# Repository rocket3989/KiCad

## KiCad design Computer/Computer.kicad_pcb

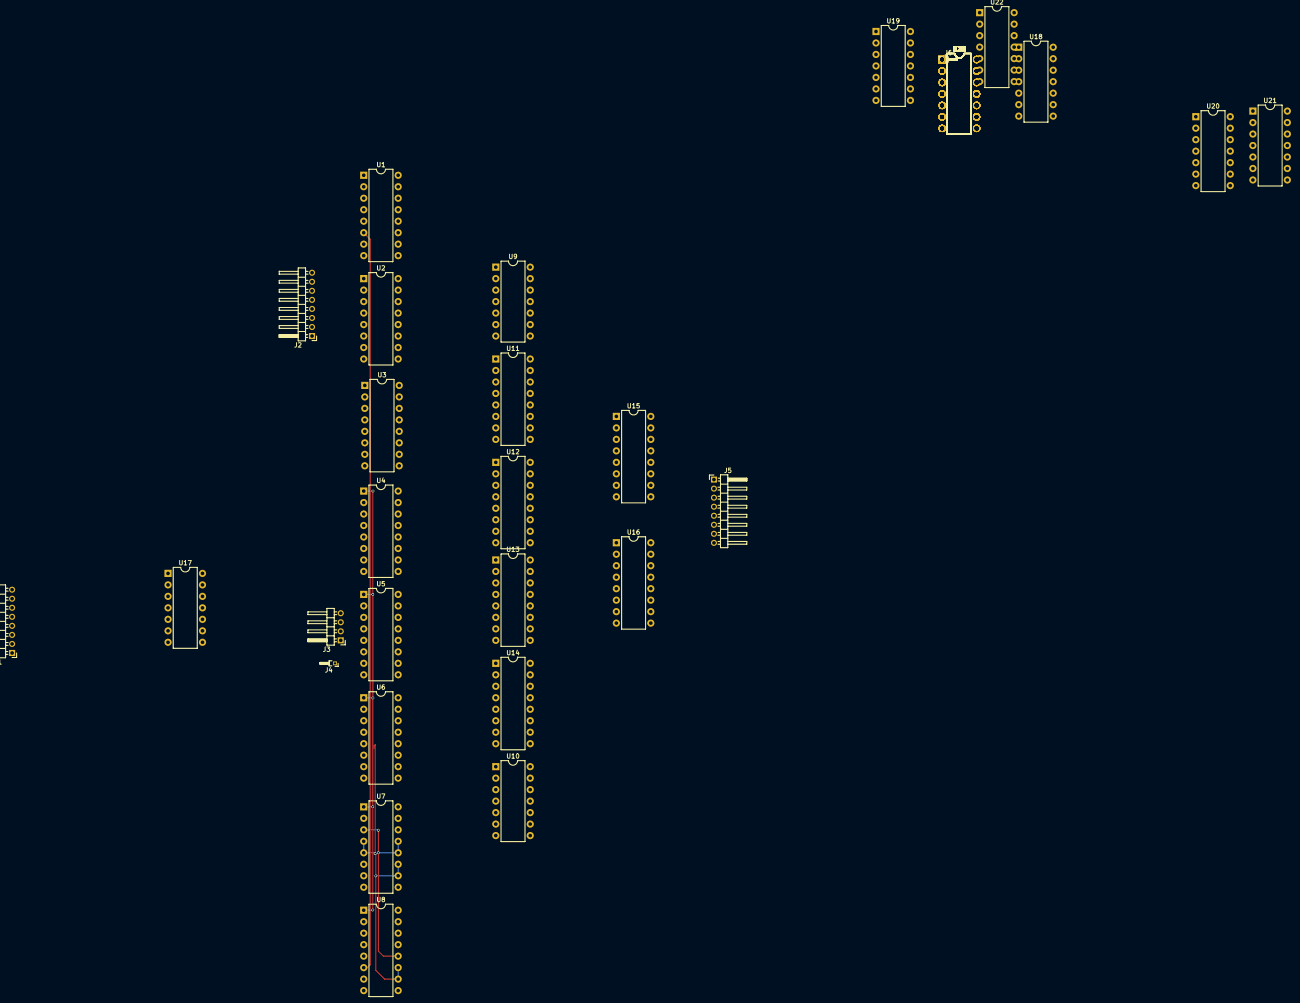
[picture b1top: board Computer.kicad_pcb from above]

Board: 2 copper layers, 44 parts (0 on the bottom side), 57 nets.

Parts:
J1: Conn_01x08; Pin_Header_Angled_1x08_Pitch2.00mm
J2, J5: Conn_01x01; Pin_Header_Angled_1x08_Pitch2.00mm
J3: Conn_01x04; Pin_Header_Angled_1x04_Pitch2.00mm
J4, J6: Conn_01x01; Pin_Header_Angled_1x01_Pitch1.00mm
U1, U2, U3, U4, U5, U6, U7, U8: 74LS253; DIP-16_W7.62mm
U9: 74LS04; DIP-14_W7.62mm
U10: 74LS08; DIP-14_W7.62mm
U11, U12: 74LS283; DIP-16_W7.62mm
U13, U14: 74LS257; DIP-16_W7.62mm
U15: 74LS04; DIP-16_W7.62mm
U16: 74LS244; DIP-16_W7.62mm
U17, U18, U19, U23, U24, U25, U26, U27, U28, U29, U30, U31, U32, U33, U34, U35, U36, U37, U38: 74LS574; DIP-14_W7.62mm
U20: 74LS161; DIP-14_W7.62mm
U21, U22: 74LS154; DIP-14_W7.62mm

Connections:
/ALU/A0: U1.14, U10.4, U11.5, U13.6
/ALU/A1: U2.14, U11.3, U13.2, U13.13
/ALU/A2: U3.14, U11.14, U13.5, U13.10
/ALU/A3: U4.14, U11.12, U13.14, U14.3
/ALU/A4: U5.14, U12.5, U13.11, U14.6
/ALU/A5: U6.14, U12.3, U14.2, U14.13, U17.14
/ALU/A6: U7.14, U12.14, U14.5, U14.10, U17.13
/ALU/A7: U8.14, U10.1, U12.12, U14.14, U17.12
/ALU/AL: J2.1, U17.11
/ALU/ALUB0: U1.9, U11.6
/ALU/ALUB1: U2.9, U11.2
/ALU/ALUB2: U3.9, U11.15
/ALU/ALUB3: U4.9, U11.11
/ALU/ALUB4: U5.9, U12.6
/ALU/ALUB5: U6.9, U12.2
/ALU/ALUB6: U7.9, U12.15
/ALU/ALUB7: U8.9, U12.11
/ALU/BUS0: J1.8, U1.2, U17.2
/ALU/BUS1: J1.7, U2.2, U17.3
/ALU/BUS2: J1.6, U3.2, U17.4
/ALU/BUS3: J1.5, U4.2, U17.5
/ALU/BUS4: J1.4, U5.2, U17.6
/ALU/BUS5: J1.3, U6.2, U17.7, U18.14
/ALU/BUS6: J1.2, U7.2, U17.8, U18.13
/ALU/BUS7: J1.1, U8.2, U17.9, U18.12
/ALU/OB: J6.1, U18.1
/ALU/OL: J5.1, U18.11
/ALU/OUT0: U1.7, U13.4, U18.2
/ALU/OUT1: U2.7, U13.7, U16.16, U18.3
/ALU/OUT2: U3.7, U13.12, U16.14, U18.4
/ALU/OUT3: U4.7, U13.9, U16.12, U18.5
/ALU/OUT4: U5.7, U14.4, U16.9, U18.6
/ALU/OUT5: U6.7, U14.7, U16.7, U18.7
/ALU/OUT6: U7.7, U14.12, U16.5, U18.8
/ALU/OUT7: U8.7, U14.9, U16.3, U18.9
/ALU/S0: J3.4, U1.3, U1.12, U1.13, U2.3, U2.12, U2.13, U3.3, U3.12, U3.13, U4.3, U4.12, U4.13, U5.3, U5.12, U5.13, U6.3, U6.12, U6.13, U7.3, U7.12, U7.13, U8.3, U8.12, U8.13, U9.1, U13.1, U14.1
/ALU/S1: J3.3, U1.4, U1.5, U1.10, U1.11, U2.4, U2.5, U2.10, U2.11, U3.4, U3.5, U3.10, U3.11, U4.4, U4.5, U4.10, U4.11, U5.4, U5.5, U5.10, U5.11, U6.4, U6.5, U6.10, U6.11, U7.4, U7.5, U7.10, U7.11, U8.4, U8.5, U8.10, U8.11, U10.2, U10.5
/ALU/S2: J3.2, U1.6, U2.6, U3.6, U4.6, U5.6, U6.6, U7.6, U8.6, U10.10, U15.5
/ALU/S3: J3.1, U1.1, U2.1, U3.1, U4.1, U5.1, U6.1, U7.1, U8.1, U10.9, U10.12
GND: J4.1, U1.8, U1.15, U2.8, U2.15, U3.8, U3.15, U4.8, U4.15, U5.8, U5.15, U6.8, U6.15, U7.8, U7.15, U8.8, U8.15, U9.7, U10.7, U11.8, U12.8, U13.8, U14.8, U15.7, U16.10, U17.1, U17.10, U18.10, U19.10, U20.8, U21.12, U22.12, U23.10, U24.10, U25.10, U26.10, U27.10, U28.10, U29.10, U30.10, U31.10, U32.10, U33.10, U34.10, U35.10, U36.10, U37.10, U38.10
unnamed: U10.3, U13.3
unnamed: U10.6, U14.11
unnamed: U10.8, U15.1
unnamed: U10.11, U15.3
unnamed: U10.13, U15.6
unnamed: U11.1, U16.4
unnamed: U11.4, U16.2
unnamed: U9.2, U11.7
unnamed: U11.9, U12.7
unnamed: U11.10, U16.8
unnamed: U11.13, U16.6
unnamed: U12.1, U16.13
unnamed: U12.4, U16.11
unnamed: U12.13, U16.15
unnamed: U13.15, U14.15, U15.2
unnamed: U15.4, U16.1
VCC: U1.16, U2.16, U3.16, U4.16, U5.16, U6.16, U7.16, U8.16, U9.14, U10.14, U11.16, U12.16, U13.16, U14.16, U15.14

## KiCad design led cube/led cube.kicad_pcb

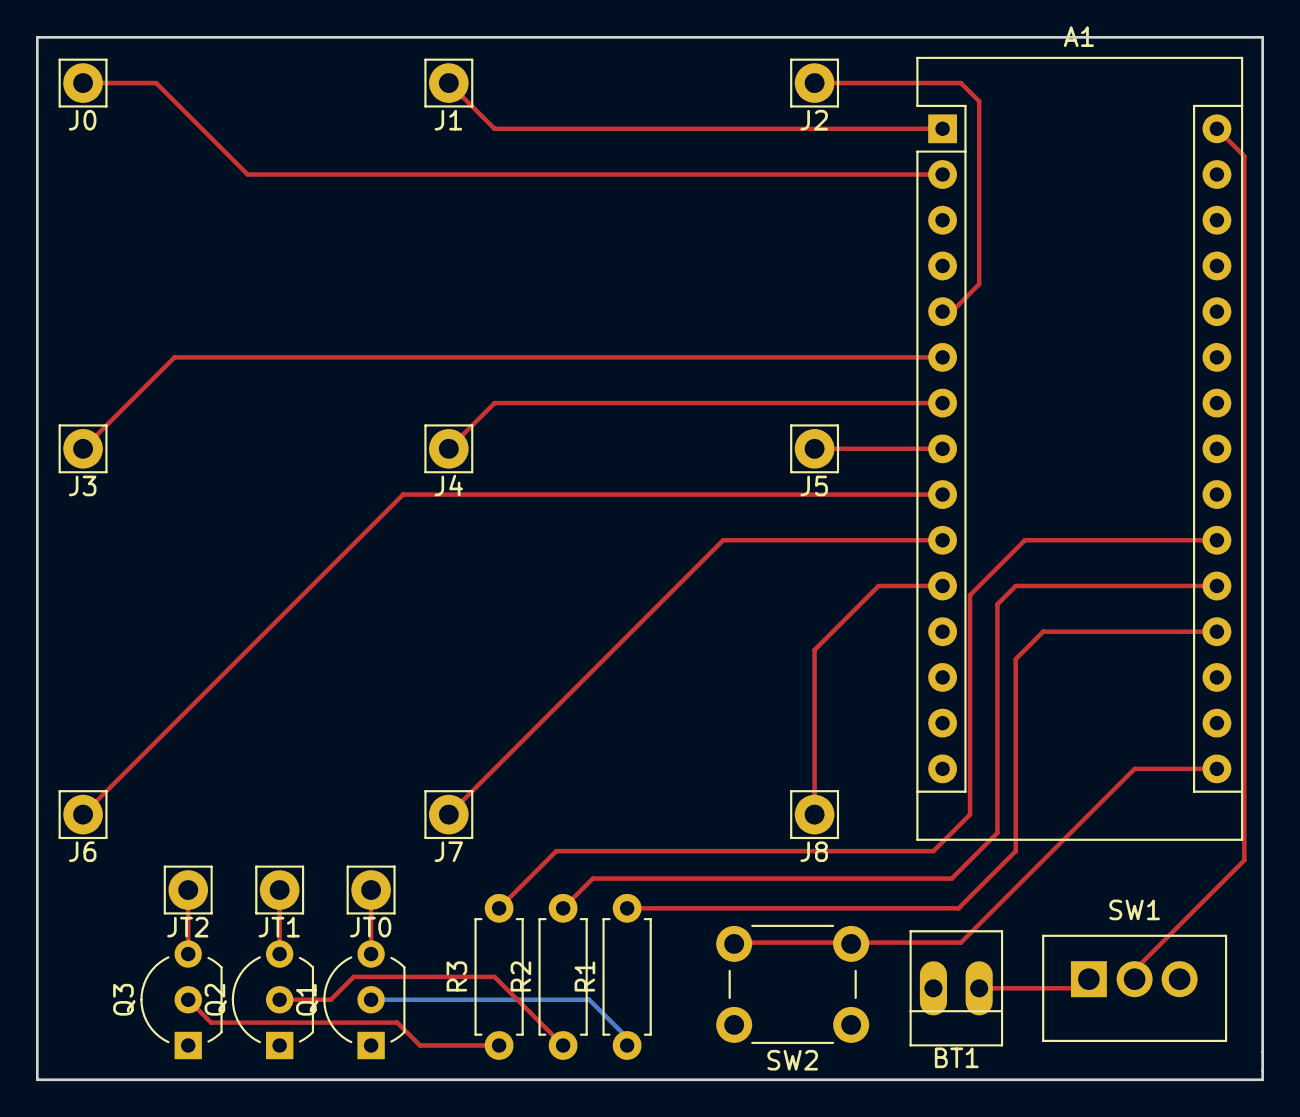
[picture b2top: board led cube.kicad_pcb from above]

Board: 2 copper layers, 68.1 x 57.9 mm, 22 parts (0 on the bottom side), 22 nets.

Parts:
A1: Arduino_Nano
BT1: Battery; PINHEAD1-2
J0, J1, J2, J3, J4, J5, J6, J7, J8: Conn_01x01; Pin_d1.1mm_L8.5mm_W2.5mm_FlatFork
JT0, JT1, JT2: Conn_01x01; Pin_d1.1mm_L8.5mm_W2.5mm_FlatFork
Q1, Q2, Q3: PN2222A; TO-92_Inline_Wide
R1, R2, R3: R; R_Axial_DIN0207_L6.3mm_D2.5mm_P7.62mm_Horizontal
SW1: SW_DIP_x01; Wafer_Vertical10x5.8x7RM2.5-3
SW2: SW_DIP_x01; SW_PUSH_6mm_h5mm

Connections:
GND: A1.4, A1.29, BT1.2, Q1.1, Q2.1, Q3.1, SW2.1
unnamed: A1.1, J1.1
unnamed: A1.2, J0.1
unnamed: A1.5, J2.1
unnamed: A1.6, J3.1
unnamed: A1.7, J4.1
unnamed: A1.8, J5.1
unnamed: A1.9, J6.1
unnamed: A1.10, J7.1
unnamed: A1.11, J8.1
unnamed: A1.16, SW2.2
unnamed: A1.19, R1.2
unnamed: A1.20, R2.2
unnamed: A1.21, R3.2
unnamed: A1.30, SW1.2
unnamed: BT1.1, SW1.1
unnamed: JT0.1, Q1.3
unnamed: JT1.1, Q2.3
unnamed: JT2.1, Q3.3
unnamed: Q1.2, R1.1
unnamed: Q2.2, R2.1
unnamed: Q3.2, R3.1
